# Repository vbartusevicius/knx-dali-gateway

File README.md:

# KNX–DALI Gateway

Open-source DIN-rail gateway between a wired **KNX TP** line and one **DALI / DALI-2** line: up to 64 control gear plus DALI-2 multi-master input devices, commissioned entirely through **ETS**. An optional integrated, isolated DALI bus supply runs from 20–32 V auxiliary DC (a 24 V PSU or the KNX white/yellow pair); the same input also powers the gateway core, with the KNX bus as a seamless fallback. The WiFi dashboard and MQTT are extras: lighting control and ETS provisioning never depend on them.

> [!NOTE]
> **Pre-hardware prototype.** Verified by native unit tests, a Docker KNX/DALI integration lab, KiCad DRC and isolation checks, JLCPCB footprint and pinout checks, and exact-solid CadQuery fit tests. No board has been powered on yet, and no KNX or DALI certification is claimed.

<p align="center">
  <a href="#downloads">Downloads</a> ·
  <a href="#screenshots">Screenshots</a> ·
  <a href="#hardware">Hardware</a> ·
  <a href="#building-one">Building one</a> ·
  <a href="#how-it-works">How it works</a> ·
  <a href="#development">Development</a>
</p>

---

## Downloads

| What | Where | Use |
| --- | --- | --- |
| **First install (USB)** | [`firmware-full-usb.bin`](https://github.com/vbartusevicius/knx-dali-gateway/releases/latest) | Bootloader, partition table and firmware in one image for an empty ESP32-C6. Connect the XIAO over USB-C and write it at `0x0`: `esptool.py --chip esp32c6 write_flash 0x0 firmware-full-usb.bin`. Clears all settings. |
| **Update** | [`firmware.bin`](https://github.com/vbartusevicius/knx-dali-gateway/releases/latest) | Drop it onto the **Firmware** tab of the web interface. Updates firmware and web UI together; settings are kept. |
| **ETS product database** | [`KnxDaliGateway.knxprod`](https://github.com/vbartusevicius/knx-dali-gateway/releases/latest) | Import into ETS 5.7 / 6: 64 lamp channels (DT6/DT7/DT8), 16 groups, broadcast, 8 DALI-2 input devices with up to 4 instances each (1,321 group objects). |
| **Hardware bundles** | [`knx-dali-gateway-v2-hardware.zip` / `v3-hardware.zip`](https://github.com/vbartusevicius/knx-dali-gateway/releases/latest) | Per-variant manufacturing & assembly package (`boards/` with Gerbers, ODB++, BOM/CPL, STEP, KiCad files and renders; `enclosure/` with STLs, STEPs, fit drawings and renders; `assembly_parts.csv` and order CSVs). |
| **Checksums** | [`SHA256SUMS.txt`](https://github.com/vbartusevicius/knx-dali-gateway/releases/latest) | SHA-256 checksums covering every release file above. |

---

## Screenshots

The web interface is built into the firmware and served by the ESP32-C6 itself (live WebSocket updates, no cloud):

<details>
<summary><b>More of the web interface</b>: lamp settings, groups and scenes, error log, bus monitor, settings</summary>

<br>

| Lamp settings | Groups & scenes |
| :---: | :---: |
|  |  |
| Device type, dimming curve, limits, fade, D4i or calculated power, ballast replacement | 16 scenes, 16 groups (G00–G15), group colour, membership written to the ballast |
| **Error log** | **Live DALI bus monitor** |
|  |  |
| Persistent NVS history with remedies | 8/16/24-bit frames and collisions: 1,024 rows on the device, 10,000 in the browser |
| **Settings** | |
|  | |
| WiFi, MQTT with Home Assistant auto-discovery, power model | |

- **Overview:** live level, DT8 colour (Tc, RGBW, xy), per-lamp power (native D4i Part 252 or calculated), lamp finder, fault codes; a second grid for DALI-2 buttons and sensors (IEC 62386-103 / 301–304).
- **Home Assistant:** one gateway device (total power and energy) plus every populated lamp with on/off, dimming, colour, power and fault entities.

</details>

<details>
<summary><b>Front-panel OLED pages</b>: V3 portrait 64×128, V2 landscape 128×64</summary>

<br>

The left button (SCROLL, plain bump) steps through the pages; holding it for 5 s starts the WiFi setup portal. The right button (RESET, bump with an X) reboots on a tap and toggles KNX programming mode when held for 5 s; both held for 10 s is a factory reset.

</details>

---

## Hardware

Two variants share the circuit blocks (`hardware/circuits/blocks/`), the XIAO ESP32-C6 pinout (`gateway/src/firmware/Board.hpp`) and the firmware:

| | **V3** (`v3`) | **V2** (`v2`) |
| --- | --- | --- |
| Width | 1 DIN (18 mm) | 2 DIN (36 mm) |
| Boards | 2: two-sided vertical `main`, front `ui` | 3: `main`, `interface`, `ui` |
| AUX core converter | TRACO TMR 2411 (2 W), on a tongue of `main` in the front protrusion | TRACO TRN 3-2411 (3 W), on the back of `main` |
| DALI terminal | WAGO 2086 push-in (SMD, hand-soldered), buttons beside the wire entries | MX126 screw |
| KNX / AUX | PST 1,0 pin strips (red/black, yellow/white plugs) | PST 1,0 KNX, MX126 screw AUX |
| Display | 0.96" 64×128 portrait SSD1312, solder flex tail | 0.96" 128×64 SSD1306 module, 4-pin header |
| Buttons | Omron B3U pressed through C-shaped spring tabs in the cover | same |
| Main ↔ UI link | 8-pin 0.5 mm FFC (Type B, 50 mm) | 10-pin JST-SH cable |
| Case | Side-opening clamshell, snap-fit | Two 2.5×10 screws, UI snaps |
| Release | [`hardware/releases/v3/`](hardware/releases/v3/README.md) | [`hardware/releases/v2/`](hardware/releases/v2/README.md) |

<details>
<summary><b>V3 renders</b>: assembly and boards</summary>

<br>

PCB artwork: [`main` top](hardware/releases/v3/main/renders/top.svg) · [bottom](hardware/releases/v3/main/renders/bottom.svg) · [`ui` top](hardware/releases/v3/ui/renders/top.svg) · [bottom](hardware/releases/v3/ui/renders/bottom.svg).
Fit drawings: [front](hardware/releases/v3/enclosure/fit_front.svg) · [side](hardware/releases/v3/enclosure/fit_side.svg).

</details>

<details>
<summary><b>V2 renders</b>: assembly and boards</summary>

<br>

PCB artwork: [`main` top](hardware/releases/v2/main/renders/top.svg) · [bottom](hardware/releases/v2/main/renders/bottom.svg) · [`interface` top](hardware/releases/v2/interface/renders/top.svg) · [bottom](hardware/releases/v2/interface/renders/bottom.svg) · [`ui` top](hardware/releases/v2/ui/renders/top.svg) · [bottom](hardware/releases/v2/ui/renders/bottom.svg).
Fit drawings: [front](hardware/releases/v2/enclosure/fit_front.svg) · [side](hardware/releases/v2/enclosure/fit_side.svg).

</details>

Pin table, LED chain and button ladder: [`hardware/docs/variants.md`](hardware/docs/variants.md). Pre-manufacturing reviews: [`review-2026-10-23.md`](hardware/docs/review-2026-10-23.md), [`review-2026-10-22.md`](hardware/docs/review-2026-10-22.md); rework for boards made from `59eea1f`: [`rework-rev-c.md`](hardware/docs/rework-rev-c.md).

---

## Building one

Each `hardware/releases/<variant>/` folder is a complete manufacturing package.

1. **PCBs with SMT assembly (JLCPCB).** Upload `panel/panel_gerbers.zip` (V3: 66.0 × 78.1 mm, 4 layers, 1.2 mm; V2: 98.5 × 76.6 mm, 4 layers, 1.6 mm) with **assembly on both sides**, `panel/panel_bom_jlc.csv` and `panel/panel_cpl_jlc.csv`. You order one PCB and one PCBA job and snap the boards apart. Per-board files are in `main/`, `ui/` (and `interface/` on V2). Compare `renders/top.svg` / `bottom.svg` with JLCPCB's placement preview.
   **Building it yourself:** `order_lcsc.csv` (LCSC BOM tool: map *LCSC Part Number* and *Quantity*) and `order_elsewhere.csv` (electronics LCSC does not sell, with Mouser / Digi-Key / TME numbers) cover every electronic part of one gateway; screws, foam and printed parts are only in `assembly_parts.csv`.
   **Other board houses** (Aisler, PCBWay, Eurocircuits, ...): every folder also has `<board>_odb.zip` (ODB++), Gerbers with drills and an IPC-D-356 netlist in `<board>_gerbers.zip`, and a generic `<board>_bom.csv` / `<board>_cpl.csv` with manufacturer part numbers and KiCad rotations.
2. **Hand-fitted parts.** `assembly_parts.csv` lists everything JLCPCB does not place (Kind `electronics`, `utility` or `printed`), with Mouser, Digi-Key and TME numbers:
   - the XIAO ESP32-C6 (pre-soldered) and its sockets;
   - the RECOM REC3-2415SRW/H2/A/CTRL DALI supply converter;
   - the TRACO AUX core converter;
   - Phoenix PST pin strips and plugs;
   - the OLED, the main-to-UI cable, and two jumper caps for `JP1`.
3. **Case.** Print `enclosure/base.stl` and one cover in PETG or ASA at 0.2 mm layers: `cover.stl`; V2 also has `cover_embossed.stl` (0.6 mm recessed legend). V3 has no front text: the button bumps tell the buttons apart.

<details>
<summary><b>V3 assembly order</b></summary>

1. Lay the OLED face down in the cover recess, fold its flex tail through the UI board's top notch and solder it to `J2`, put the 4 mm foam pad on the UI board, snap the UI board in.
2. Slide `main` into the base from the open left side, so the KNX/AUX pins pass into the right-side pockets and `J3` seats in the top opening.
3. Plug the FFC into `main J4` and `ui J1`, then close the cover over the left side and front until the four side snaps lock.

</details>

---

## How it works

- **KNX side:** an onsemi NCN5130 transceiver (TP1, 9-bit UART) charges a 470 µF store. An SCT2400 buck makes 5 V from it, with an undervoltage lockout above the NCN5130 reset level.
- **Core supply:** the AUX input feeds an isolated TRACO converter (SELV-AUX to SELV-KNX). A leaded priority path prefers it (TLV803 supervisor, 2N7002 and AO3401A switch) and a B5819W Schottky falls back to the KNX buck without a gap. A TI LM66100 keeps USB service power out of the core rail.
- **DALI supply:** the AUX input (PTC, TVS, reverse diode) feeds a RECOM REC3-2415SRW/H2/A/CTRL (24 V → 15 V, functional isolation), then a linear current limiter. The firmware can switch it off through an optocoupler on its `CTRL` pin, and jumper `JP1` disconnects it for an external DALI PSU.
- **DALI transceiver:** TX uses a MOSFET sink with bootstrap gate drive and a 275–350 mA fault clamp. RX uses a zener threshold with a constant-current detector. Both cross a 5.5 mm (reinforced, IEC 60664-1 230 V OVC III) milled barrier through TLP383 optocouplers.
- **Front panel:** the OLED (I2C), two buttons on one ADC ladder, and three WS2812B-MINI-V3J RGB LEDs with gull-wing legs (status, KNX, DALI) behind a 5 V level shifter. All passives are 0805 or larger except three 0603 bus caps next to the NCN5130 on V3; the NCN5130 (QFN-40) is the only leadless chip, as no leaded KNX transceiver exists.

---

## Development

| Folder | Contents |
| --- | --- |
| `gateway/` | ESP32-C6 firmware (C++17, ESP-IDF / PlatformIO) and native unit tests |
| `knxprod/` | ETS product database source and `.knxprod` builder |
| `simulation/` | DALI bus simulator and Docker KNX/DALI integration lab |
| `hardware/` | SKiDL circuits, KiCad layouts, part data, build scripts, release packages |
| `mechanical/` | CadQuery enclosures, fit drawings, front legends, 3D renders |

| Task | Command |
| --- | --- |
| Build, route (fastroute), render, release and test both hardware variants | `python3 hardware/scripts/build.py` |
| One variant or step | `python3 hardware/scripts/build.py v3 --eda` (`--cad`, `--release`, `--test`) |
| Refresh the README images (after a release) | `docker compose --profile hardware run --rm -T cad "python3 mechanical/scripts/readme_images.py"` |
| Firmware tests and ESP32-C6 build (writes `firmware.bin` and `firmware-full-usb.bin`) | `pio test -d gateway -e native && pio run -d gateway -e dev_c6 -e release_c6` |
| Refresh the clangd compilation database | `pio run -d gateway -e dev_c6 -t compiledb` |
| Integration lab | `simulation/run-tests.sh` |
| ETS package | `ETS_CV_DIR=knxprod/ETS knxprod/scripts/package.sh` |
| Stage GitHub release assets + `SHA256SUMS.txt` | `python3 scripts/package_release.py --clean` |
| Lint Python (ruff) | `docker compose --profile lint run --rm lint check .` |
| Lint C++ (clang-format, clang-tidy) | `docker compose --profile lint run --rm cpp-lint gateway/scripts/check_cpp.sh` |

Licences per folder: [`LICENSE.md`](LICENSE.md). Contributor and coding-agent instructions (rules, commands, requirements): [`AGENTS.md`](AGENTS.md). Design background and research history: [`docs/research-notes.md`](docs/research-notes.md).

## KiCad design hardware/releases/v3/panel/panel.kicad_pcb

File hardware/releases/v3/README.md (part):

# KNX-DALI gateway hardware v3 (1 DIN, two boards)

**Revision D (2026-10-22).** Changes against rev C (`59eea1f`, the first order): AUX-powered core (TRACO TMR 1-2411 U9 isolated converter, hand-fitted, plus TI TPS2121 U10 priority mux with the KNX buck as fallback); XIAO LM66100 U7 CE on VOUT (no USB back-feed); DALI TX clamp 2R, gate divider 4k7/10k, RX pull-up 4k7, buck EN 100k; enclosure with channels over the back-side diodes, board edge reliefs, backing ribs, C-shaped spring button tabs with front bumps and plungers, OLED supports beside the panel, longer DALI terminal slot; through-hole leads trimmed to 1.5 mm; a base right-wall recess over U9. Rev C boards and prints: follow [`hardware/docs/rework-rev-c.md`](../../docs/rework-rev-c.md) (pins in `rework/`). NCN5130 cluster re-placed to the datasheet layout rules (C1/C2/C3/C5/C15, L1).

**Hand-assembly revision (2026-11-11).** Every part is chosen for soldering with an iron:
- **Passives:** all 0805 or larger. The one exception is v3's three NCN5130 bus caps (C1 47 nF, C2 100 nF, C3 220 nF), which are 0603 so the chip's left side stays routable.
- **LEDs:** WS2812B-MINI-V3J with gull-wing legs (LCSC C22371519).
- **Crystal:** 2-pad 5032.
- **Core power path:** leaded parts (TLV803M U10, 2N7002 Q10, AO3401A Q9, B5819W D11) replace the VQFN TPS2121.
- **Still fine-pitch:** the NCN5130 (QFN-40; no leaded KNX transceiver exists: hot plate or hot air) and the LM66100 (SC-70-6, leaded).
- **Isolation:** DALI isolation is 5.5 mm (reinforced, IEC 60664-1 230 V OVC III PD2); SELV-AUX to SELV-KNX is 1 mm (functional).
- **Buttons:** left = SCROLL (plain bump), right = RESET (X bump).
- **USB service:** the XIAO is turned so its USB-C faces the main board's rail-side edge (x 38.1, 1.7 mm from the edge, nothing tall in the path). Lift main out of the base to plug in: with the board in the base the plug overmould does not fit under the right wall. test_usb_access.py keeps the plug path clear.
- `<board>/<board>_assembly.pdf`: hand-soldering guide. One page per populated side (the bottom mirrored, as seen from below), each part's body, reference and value, a red dot on pin 1, a black corner on hand-fitted parts and one colour per value. Large parts are dashed under the small ones. A values page lists quantity, side and references.

Generated by `HARDWARE_VARIANT=v3 python3 hardware/scripts/release.py v3` from
`hardware/layout/v3/`, with the same gates as v2: KiCad DRC 0 errors and 0
unrouted, every part orderable or hand-fit, every JLC part checked against
JLCPCB's part record, live stock and its EasyEDA footprint (pin for pin; the
placement file carries the fitted rotations and centres). CI
(`HARDWARE_VARIANT=v3`, `test_release_current.py`) fails as soon as either board
no longer matches this release.

| Board | Size | Layers | Thickness | Position in the case | Folder |
|---|---|---|---|---|---|
| **Breakaway Panel (`panel`)** | **55.6 x 78.0 mm** | **4** | **1.2 mm** | **Combined `main` + `ui` on one PCB with mouse-bite breakaway tabs (1 PCB + 1 PCBA order)** | **`panel/`** |
| Main (`main`) | 39.8 x 78.0 mm | 4 | 1.2 mm | vertical along the left side wall (two-sided): tall parts on the front (+x: KNX/AUX/DALI push-in pin strips, 470 uF SMD cap, 220 uH inductor, XIAO on 5 mm sockets with 5 V buck underneath, REC3-2415SRW/H2/A/CTRL, JP1, DALI bridge/pass transistor/optocouplers, UI FFC), low SMD parts on the back (-x, inside the THT solder-tail shadow: NCN5130 + crystal + passives, DALI TX/RX passives & transistors) | `main/` |
| UI (`ui`) | 13.8 x 40.5 mm | 4 | 1.2 mm | snapped into the cover protrusion: 0.96" 64x128 portrait SSD1312 OLED (QG-6428TSWCG02 / JLX12864OLED-S096W / NFP1312-15AY, 14.0 x 28.0 mm) soldered to the 14-pad 0.62 mm pitch footprint on the back with 3.3 V charge-pump passives, two Omron B3U-1000P buttons with 1.4 mm protruding caps, three RGB LEDs in a row below the buttons, 8-pin FFC to main | `ui/` |

A single 8-pin 0.5 mm **Type B (reverse / opposite-side contacts)** FFC cable (`SHOU HAN FFC-0.5-8P-50mm-B`, LCSC `C42416274`, 50 mm) connects `main` J4 to `ui` J1 (since both `J4` and `J1` are bottom-contact FFC connectors with Pin 1 on the same side, a Type B reverse cable connects Pin 1 `+3V3` to Pin 1 `+3V3`).

## Ordering at JLCPCB

1. **Recommended — Order as 1 Breakaway Panel (`panel/`):**
   - Upload `panel/panel_gerbers.zip` and select **4 layers, `1.2 mm` PCB Thickness** on JLCPCB's order page (note: JLCPCB's web form always defaults the thickness radio button to `1.6 mm` until you click **`1.2`**).
   - Enable **PCB Assembly (Both Sides)** and upload `panel/panel_bom_jlc.csv` + `panel/panel_cpl_jlc.csv`.
2. **Or Order as Separate Boards (`main/` and `ui/`):**
   - Upload `main/main_gerbers.zip` and `ui/ui_gerbers.zip` (4 layers, **1.2 mm**).
   - Upload `<board>_bom_jlc.csv` + `<board>_cpl_jlc.csv`.
3. `<board>_assembly_check.csv` (and `panel/panel_assembly_check.csv`) lists JLCPCB footprint, rotation and stock for
   every part.

## Ordering elsewhere (Aisler, PCBWay, Eurocircuits, ...)

Each board folder and `panel/` also holds fab-independent files:

- `<board>_odb.zip`: ODB++ (copper, drills, outline, netlist, component
  placement). Aisler's preferred upload; PCBWay and Eurocircuits accept it.
- `<board>_gerbers.zip`: Gerber X2 per layer, Excellon drills (plated and
  non-plated) and `<board>.d356`, the IPC-D-356 netlist for the electrical test.
- `<board>_bom.csv`: every part with value, footprint, manufacturer part number
  (LCSC number for reference), SMD/THT, and whether the assembler or you fit it.
- `<board>_cpl.csv`: placement of the assembled parts in KiCad's coordinates
  and rotations (the `_jlc` files use JLCPCB's rotations and are for JLCPCB only).

Order the stack-up, thickness and finish given above; check the assembler's
placement preview for the bottom-side and rotated parts as for JLCPCB.

## Ordering the parts yourself

For one complete gateway (all boards and hand-fit parts), in this folder:

- `order_lcsc.csv`: LCSC BOM tool (lcsc.com → BOM Tool, map **LCSC Part Number** and
  **Quantity**). Every board part plus the hand-fit parts LCSC sells; one line per LCSC number,
  designators as `board:ref`. Multiply the quantities for more gateways; LCSC rounds up to each
  part's minimum order.
- `order_elsewhere.csv`: the electronics LCSC does not sell (XIAO, REC3, converters, Phoenix pin
  strips and plugs, OLED, cable), with every Mouser / Digi-Key / TME number. A cell may list
  alternatives, e.g. `713-102010636 (or 713-113991254)`; buy one of them.
- `assembly_parts.csv`: everything not placed by the assembler, with a **Kind** column:
  `electronics` (the hand-fit parts above), `utility` (screws, foam pad, lead trimming) and
  `printed` (case parts). Utility and printed items are not in the order files; get them locally.

Not needed when JLCPCB assembles the boards: then order only the hand-fit lines.

## Hand-fitted parts (`<board>_hand_fit.csv`)

- `main` J1, J2: two **Phoenix Contact 1574200** (PST 1,0/2-5,75) pin strips on
  the bottom shoulder of `main` (pins pointing +x to the right). The red/black KNX
  plug (front) and the yellow/grey 20-32 V AUX plug (rear) go in from the right
  side into pockets sized for the WAGO 243-211 (11.5 x 10.2 x 10.2 mm, measured,
  0.3 mm clearance all round, a slot for the butterfly key on the lower wall)
  and sit on the strips, where their sockets meet the pins. Their wire entries
  face down, about 2.8 mm inside the open bottom of the pockets. With the
  11.5 mm plug, about 1 mm of it stands out of the case's right side: leave
  that gap to the next device on the rail.
- `main` J3: **WAGO 2086-1202/700-000/997-604**, the 2-pole 3.5 mm SMD DALI
  push-in terminal. Hand-solder it (JLCPCB has none in stock; Digi-Key
  `2946-2086-1202/700-000/997-604CT-ND`). Its wire entries and both release
  buttons are in the face that sits in the top-wall opening: press a button
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
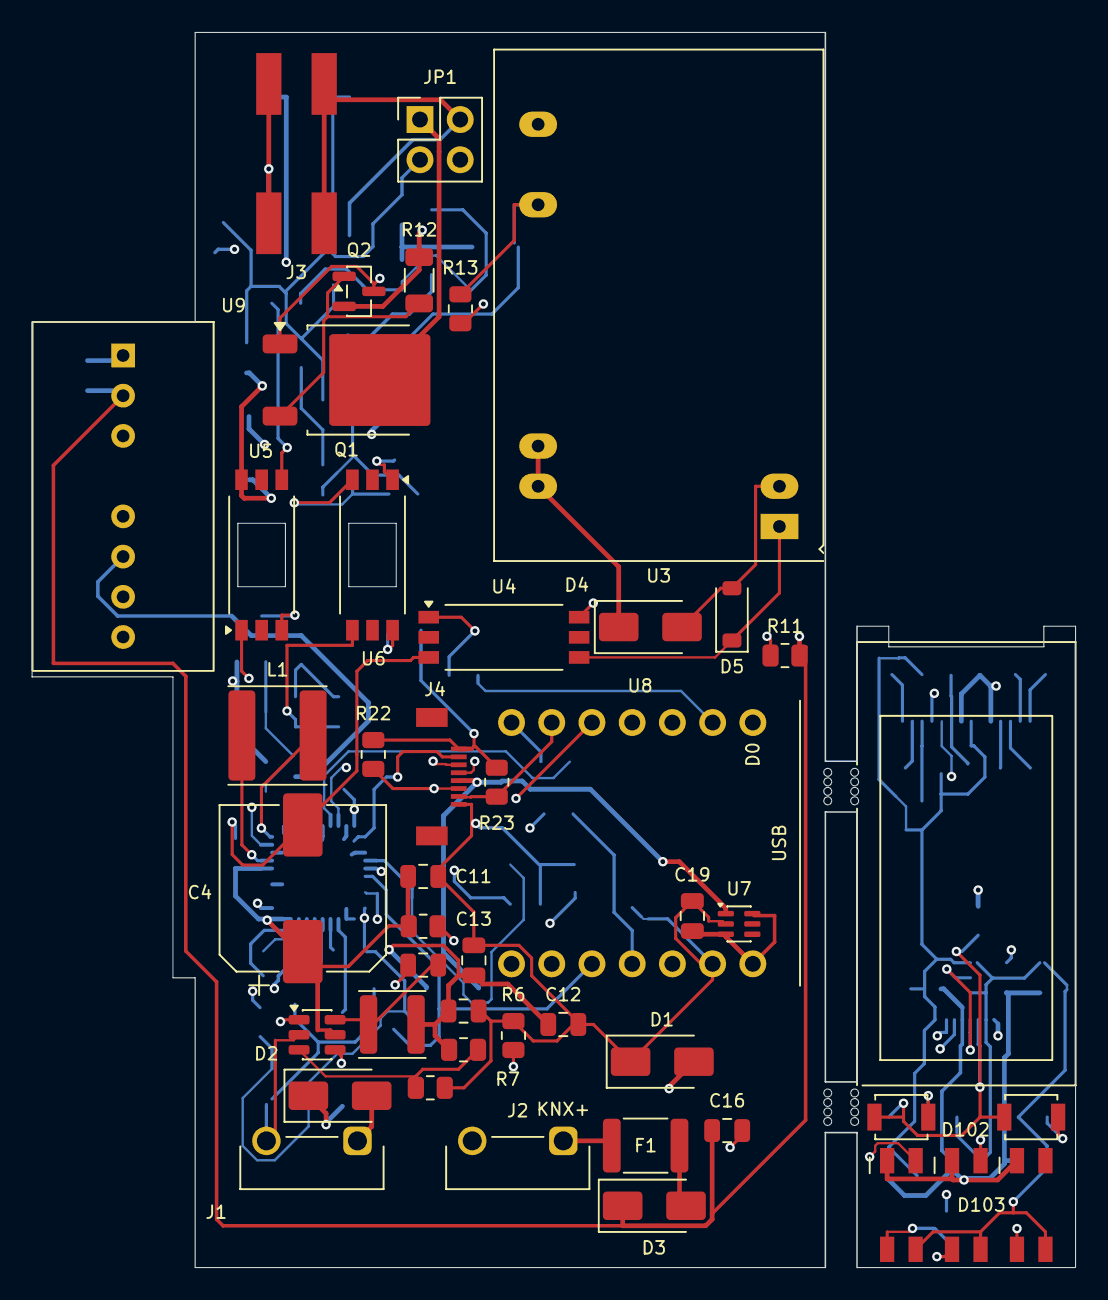
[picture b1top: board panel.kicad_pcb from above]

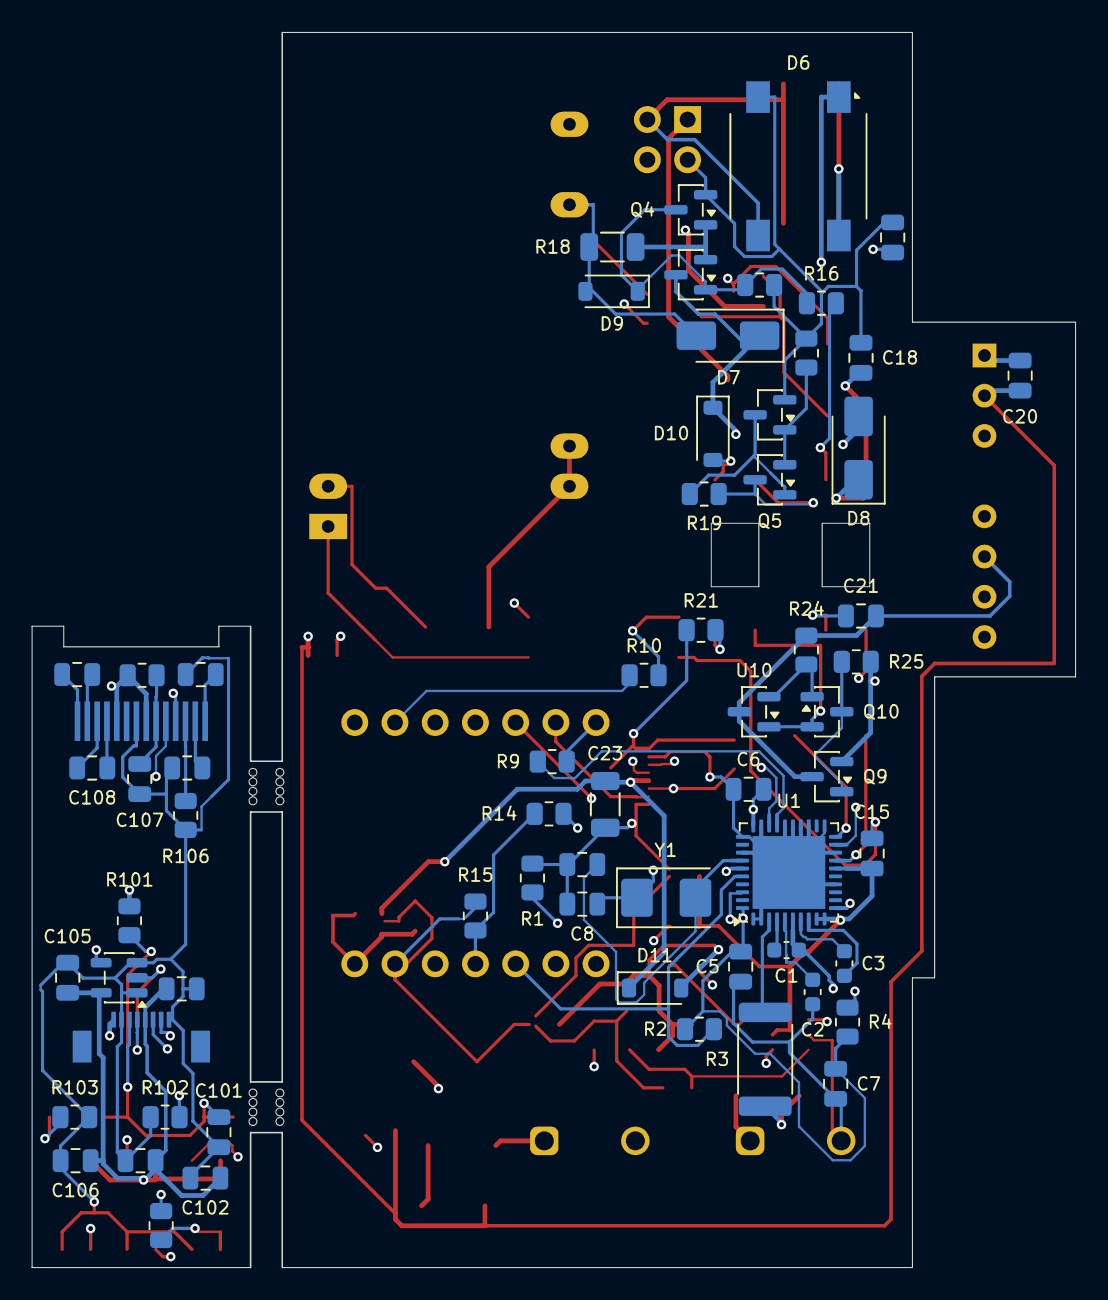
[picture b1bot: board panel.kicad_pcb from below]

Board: 4 copper layers, 65.9 x 78.0 mm, 126 parts (65 on the bottom side), 82 nets.

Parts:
C1: 47n 50V; C_0603_1608Metric
C2: 100n 50V; C_0603_1608Metric
C3: 220n 50V; C_0603_1608Metric
C4: 470u 35V; CP_Elec_10x10
C5, C6, C10, C14, C101, C103, C104, C105, C106, C107: 100n 50V; C_0805_2012Metric
C7, C12, C13: 22u 25V; C_0805_2012Metric
C8, C9: 33p C0G 50V; C_0805_2012Metric
C11, C16, C20: 10u 50V; C_0805_2012Metric
C15, C18, C102, C108, C109, C110, C111: 1u 50V; C_0805_2012Metric
C17, C19, C21: 10u 25V; C_0805_2012Metric
C23: 100u 6.3V; C_1206_3216Metric
D1: SMAJ40CA; D_SMA
D2, D3, D8: SS16; D_SMA
D4: SMAJ33A; D_SMA
D5, D10: 5V6; D_SOD-123
D6: DF06S; Diode_Bridge_Vishay_DFS
D7: SMAJ24A; D_SMA
D9: 12V; D_SOD-123
D11: B5819W; D_SOD-123
D101: RGB STATUS; LED_WS2812B-MINI-V3J_3.5x3.5mm
D102: RGB KNX; LED_WS2812B-MINI-V3J_3.5x3.5mm
D103: RGB DALI; LED_WS2812B-MINI-V3J_3.5x3.5mm
F1: 1.1A; Fuse_1812_4532Metric
J1: KNX bus terminal pins; Phoenix_PST_1,0-2-5,75_R32_1x02_P5.75mm
J2: AUX 20-32 V (yellow/white); Phoenix_PST_1,0-2-5,75_R32_1x02_P5.75mm
J3: DALI bus (push-in); TerminalBlock_WAGO_2086-1202_SMD
J4: UI board; FPC_Kinghelm_KH-FPC0.5-H1.2SMT-8P
J101: Carrier; FPC_Kinghelm_KH-FPC0.5-H1.2SMT-8P
J102: OLED; OLED_FPC_14P_P0.62mm_Hotbar
JP1: DALI supply; PinHeader_2x02_P2.54mm_Vertical
L1: 220uH; L_Sunlord_SWPA6045S
L2: 4.7uH; L_APV_ANR4012
MB1, MB2, MB3, MB4, MB5, MB6, MB7, MB8, MB9, MB10, MB11, MB12, MB13, MB14, MB15, MB16: DNP
Q1: MJD45H11; TO-252-2
Q2: BC857; SOT-23
Q3: IRLML0060; SOT-23
Q4, Q5, Q6: BC847; SOT-23
Q9: AO3401A; SOT-23
Q10: 2N7002; SOT-23
R1, R6, R8: 10k 1%; R_0805_2012Metric
R2, R11, R15, R17, R25, R101, R102, R105: 10k; R_0805_2012Metric
R3: 27R; R_2512_6332Metric
R4: 1R; R_0805_2012Metric
R5: 100k 1%; R_0805_2012Metric
R7: 51k 1%; R_0805_2012Metric
R9: 1k; R_0805_2012Metric
R10, R14, R104: 330R; R_0805_2012Metric
R12: 3R3; R_1206_3216Metric
R13, R16, R21, R22, R23: 4k7; R_0805_2012Metric
R18: 2R; R_1206_3216Metric
R19, R24: 100k; R_0805_2012Metric
R20: 680R; R_0805_2012Metric
R103: 20k; R_0805_2012Metric
R106: 390k; R_0805_2012Metric
SW101: SCROLL; SW_SPST_B3U-1000P
SW102: RESET; SW_SPST_B3U-1000P
U1: NCN5130MNTWG; QFN-40-1EP_6x6mm_P0.5mm_EP4.6x4.6mm
U2: SCT2400TVBR; TSOT-23-6
U3: REC3-2415SRW/H2/A/CTRL 24V->15V 3W iso; Converter_DCDC_RECOM_REM3_DIP24_CTRL
U4: TLP383; SO-6L_10x3.84mm_P1.27mm
U5, U6: TLP383(D4BLLTL,E; SO-6L_10x3.84mm_P1.27mm
U7: LM66100; SOT-363_SC-70-6
U8: XIAO ESP32C6; XIAO_ESP32C6_Header
U9: TMR 2411 24V->5V 2W iso; Converter_DCDC_TRACO_TMR2_SIP8
U10: TLV803M supervisor; SOT-23
U101: 74AHCT1G125; SOT-23-5
Y1: 16MHz; Crystal_SMD_5032-2Pin_5.0x3.2mm

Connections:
+3V3: J4.1, R21.1, R22.1, R23.1, U8.12
+3V3_TRX: C5.1, C6.1, C7.1, R2.1, R4.2, U1.11, U1.19, U1.30, U1.40
+5V: C23.1, D11.1, J4.5, Q9.2, R25.1, U7.1
+5V_AUX: C21.1, Q9.3, R24.1, U9.6, U10.3
+5V_BUCK: C12.1, C13.1, C14.1, D11.2, L2.2, R7.1
+5V_XIAO: C19.1, U7.3, U7.6, U8.14
AUX_FUSED: D3.2, F1.2
AUX_IN: F1.1, J2.1
AUX_P: C16.1, C20.1, D3.1, D4.1, R11.1, U3.22, U3.23, U9.2
BTN_LADDER: J4.3, U8.3
CAV: C2.1, U1.5
CCP: C1.2, U1.4
CEQ1: C3.1, U1.7
CEQ2: C3.2, U1.8
CORE_AUX_GOOD: Q10.1, R24.2, U10.2
CORE_PFET_G: Q9.1, Q10.3, R25.2
DA1: D6.3, J3.1, JP1.2
DA2: D6.4, J3.2, JP1.4
DALI_BOOT: C18.1, D8.1, U5.6
DALI_GATE: D9.1, Q3.1, Q4.3, R16.2, R17.1
DALI_GATE_SW: R16.1, U5.4
DALI_ISO15V: C17.1, Q2.2, R12.1, U3.14
DALI_RX: R21.2, U6.6, U8.9
DALI_SENSE: Q3.2, Q4.1, R18.1
DALI_SUPPLY_OFF: R10.1, U8.2
DALI_SUPPLY_SW: JP1.1, Q1.2
DALI_TX: R14.1, R15.1, U8.11
DA_P: D6.1, D7.1, D8.2, D10.1, Q3.3
FANIN: R1.1, U1.38
GND: C2.2, C4.2, C5.2, C6.2, C7.2, C8.2, C9.2, C11.2, C12.2, C13.2, C14.2, C15.2, C19.2, C21.2, C23.2, D1.1, J1.2, J4.2, J4.8, Q10.2, R1.2, R6.2, R8.2, R15.2, U1.1, U1.2, U1.14, U1.18, U1.21, U1.23, U1.24, U1.25, U1.26, U1.29, U1.31, U1.33, U1.41, U2.2, U4.3, U5.3, U6.4, U7.2, U8.13, U9.7, U10.1
GNDA: C16.2, C20.2, D4.2, D5.2, J2.2, U3.2, U9.1
GNDD: C17.2, C18.2, D6.2, D7.2, D9.2, JP1.3, Q4.2, Q6.2, R13.2, R17.2, R18.2, R20.2, U3.16
I2C_SCL: J4.7, R23.2, U8.6
I2C_SDA: J4.6, R22.2, U8.5
KNX_P: D1.2, D2.2, J1.1
KNX_P_PROT: C1.1, D2.1, R3.1, U1.6
KNX_RXD: R9.1, U8.7
KNX_TXD: U1.28, U8.8
LED_DATA: J4.4, U8.1
unnamed: R5.2, R6.1, U2.4
unnamed: C10.1, U2.1
unnamed: R7.2, R8.1, U2.3
unnamed: R9.2, U1.27
unnamed: R10.2, U4.1
unnamed: R11.2, U4.6
unnamed: D5.1, U3.1, U4.4
unnamed: Q1.3, Q2.1, R12.2
unnamed: Q1.1, Q2.3, R13.1
unnamed: R14.2, U5.1
unnamed: D10.2, U6.1
unnamed: Q5.2, Q6.1, R20.1
unnamed: Q5.1, Q6.3, R19.2
NCN_SAVEB: R2.2, U1.36, U8.10
RX_LIM_IN: Q5.3, R19.1, U6.3
SW: C10.2, L2.1, U2.6
TX0: R3.2, U1.3
UI_+3V3: J101.1, J102.5, J102.8, R101.1, R105.1
UI_+5V: C102.1, C103.1, C104.1, C105.1, C106.1, D101.1, D102.1, D103.1, J101.5, U101.5
UI_BTN_LADDER: C101.1, J101.3, R101.2, SW101.1, SW102.1
UI_GND: C101.2, C102.2, C103.2, C104.2, C105.2, C106.2, C107.2, C110.2, C111.2, D101.3, D102.3, D103.3, J101.2, J101.8, J102.7, R102.2, R103.2, R106.2, U101.1, U101.3
UI_I2C_SCL: J101.7, J102.10
UI_I2C_SDA: J101.6, J102.11
UI_LED_CHAIN1: D101.2, D102.4
UI_LED_CHAIN2: D102.2, D103.4
UI_LED_DATA: J101.4, U101.2
UI_N$1: R102.1, SW101.2
UI_N$2: R103.1, SW102.2
UI_N$3: R104.1, U101.4
UI_N$4: D101.4, R104.2
UI_OLED_C1N: C108.2, J102.4
UI_OLED_C1P: C108.1, J102.3
UI_OLED_C2N: C109.2, J102.2
UI_OLED_C2P: C109.1, J102.1
UI_OLED_IREF: J102.12, R106.1
UI_OLED_RES: C107.1, J102.9, R105.2
UI_OLED_VCOMH: C110.1, J102.13
UI_OLED_VOUT: C111.1, J102.14
VDD1M: L1.2, R4.1, U1.20
VFILT: C4.1, C11.1, C15.1, R5.1, U1.9, U1.10, U1.16, U2.5
VSW1: L1.1, U1.17
XTAL1: C8.1, U1.35, Y1.1
XTAL2: C9.1, U1.34, Y1.2

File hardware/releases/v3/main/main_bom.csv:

Designator,Quantity,Value,Footprint,Manufacturer Part Number,LCSC Part #,Mount,Fitted by
F1,1,1.1A,Fuse_1812_4532Metric,1812L110/33MR,C142747,SMD,assembler
"R19,R24",2,100k,R_0805_2012Metric,0805W8F1003T5E,C149504,SMD,assembler
R5,1,100k 1%,R_0805_2012Metric,0805W8F1003T5E,C149504,SMD,assembler
C2,1,100n 50V,C_0603_1608Metric,CC0603KRX7R9BB104,C14663,SMD,assembler
"C10,C14,C5,C6",4,100n 50V,C_0805_2012Metric,CC0805KRX7R9BB104,C49678,SMD,assembler
C23,1,100u 6.3V,C_1206_3216Metric,CL31A107MQHNNNE,C15008,SMD,assembler
"R11,R15,R17,R2,R25",5,10k,R_0805_2012Metric,0805W8F1002T5E,C17414,SMD,assembler
"R1,R6,R8",3,10k 1%,R_0805_2012Metric,0805W8F1002T5E,C17414,SMD,assembler
"C17,C19,C21",3,10u 25V,C_0805_2012Metric,CL21A106KAYNNNE,C15850,SMD,assembler
"C11,C16,C20",3,10u 50V,C_0805_2012Metric,GRM21BR61H106KE43L,C440198,SMD,assembler
D9,1,12V,D_SOD-123,MMSZ12T1G,C72599,SMD,assembler
Y1,1,16MHz,Crystal_SMD_5032-2Pin_5.0x3.2mm,TAXM16M2QLFCDT1T,C122519,SMD,assembler
R4,1,1R,R_0805_2012Metric,0805W8F100KT5E,C25271,SMD,assembler
R9,1,1k,R_0805_2012Metric,0805W8F1001T5E,C17513,SMD,assembler
"C15,C18",2,1u 50V,C_0805_2012Metric,CL21B105KBFNNNE,C28323,SMD,assembler
C3,1,220n 50V,C_0603_1608Metric,CL10B224KB8NNNC,C64705,SMD,assembler
L1,1,220uH,L_Sunlord_SWPA6045S,SWPA6045S221MT,C91047,SMD,assembler
"C12,C13,C7",3,22u 25V,C_0805_2012Metric,CL21A226MAQNNNE,C45783,SMD,assembler
R3,1,27R,R_2512_6332Metric,25121WJ0270T4E,C25478,SMD,assembler
Q10,1,2N7002,SOT-23,2N7002,C8545,SMD,assembler
R18,1,2R,R_1206_3216Metric,1206W4F200KT5E,C17942,SMD,assembler
"R10,R14",2,330R,R_0805_2012Metric,0805W8F3300T5E,C17630,SMD,assembler
"C8,C9",2,33p C0G 50V,C_0805_2012Metric,0805CG330J500NT,C157687,SMD,assembler
R12,1,3R3,R_1206_3216Metric,1206W4F330KT5E,C17945,SMD,assembler
L2,1,4.7uH,L_APV_ANR4012,SMNR4012-4R7MT,C135248,SMD,assembler
C4,1,470u 35V,CP_Elec_10x10,RYRVT35V470UF10*10,C48970703,SMD,assembler
C1,1,47n 50V,C_0603_1608Metric,CL10B473KB8NNNC,C1622,SMD,assembler
"R13,R16,R21,R22,R23",5,4k7,R_0805_2012Metric,0805W8F4701T5E,C17673,SMD,assembler
R7,1,51k 1%,R_0805_2012Metric,0805W8F5102T5E,C17737,SMD,assembler
"D10,D5",2,5V6,D_SOD-123,MMSZ5V6T1G,C236111,SMD,assembler
R20,1,680R,R_0805_2012Metric,0805W8F6800T5E,C17798,SMD,assembler
Q9,1,AO3401A,SOT-23,AO3401A,C15127,SMD,assembler
D11,1,B5819W,D_SOD-123,B5819W SL,C8598,SMD,assembler
"Q4,Q5,Q6",3,BC847,SOT-23,BC847B,C57668,SMD,assembler
Q2,1,BC857,SOT-23,BC857C,C181147,SMD,assembler
JP1,1,DALI supply,PinHeader_2x02_P2.54mm_Vertical,2.54-2*2PPin,C66690,THT,assembler
D6,1,DF06S,Diode_Bridge_Vishay_DFS,DF06S-T,C460867,SMD,assembler
Q3,1,IRLML0060,SOT-23,IRLML0060TRPBF,C67274,SMD,assembler
U7,1,LM66100,SOT-363_SC-70-6,LM66100DCKR,C2869734,SMD,assembler
Q1,1,MJD45H11,TO-252-2,MJD45H11,C48580717,SMD,assembler
U1,1,NCN5130MNTWG,QFN-40-1EP_6x6mm_P0.5mm_EP4.6x4.6mm,NCN5130MNTWG,C513000,SMD,assembler
U2,1,SCT2400TVBR,TSOT-23-6,SCT2400TVBR,C2693819,SMD,assembler
D7,1,SMAJ24A,D_SMA,SMAJ24A,C148222,SMD,assembler
D4,1,SMAJ33A,D_SMA,SMAJ33A,C113966,SMD,assembler
D1,1,SMAJ40CA,D_SMA,SMAJ40CA,C113970,SMD,assembler
"D2,D3,D8",3,SS16,D_SMA,SS16,C2481,SMD,assembler
U4,1,TLP383,SO-6L_10x3.84mm_P1.27mm,"TLP383(D4BLLTL,E",C3002263,SMD,assembler
"U5,U6",2,"TLP383(D4BLLTL,E",SO-6L_10x3.84mm_P1.27mm,"TLP383(D4BLLTL,E",C3002263,SMD,assembler
U10,1,TLV803M supervisor,SOT-23,TLV803MDBZR-TP,C52817175,SMD,assembler
J4,1,UI board,FPC_Kinghelm_KH-FPC0.5-H1.2SMT-8P,KH-FPC0.5-H1.2SMT-8P-QCHF,C48532769,SMD,assembler
J2,1,AUX 20-32 V (yellow/white),"Phoenix_PST_1,0-2-5,75_R32_1x02_P5.75mm",1574200,,THT,hand-fit (not assembled)
J3,1,DALI bus (push-in),TerminalBlock_WAGO_2086-1202_SMD,2086-1202/700-000/997-604,,SMD,hand-fit (not assembled)
J1,1,KNX bus terminal pins,"Phoenix_PST_1,0-2-5,75_R32_1x02_P5.75mm",1574200,,THT,hand-fit (not assembled)
U3,1,REC3-2415SRW/H2/A/CTRL 24V->15V 3W iso,Converter_DCDC_RECOM_REM3_DIP24_CTRL,REC3-2415SRW/H2/A/CTRL,,THT,hand-fit (not assembled)
U9,1,TMR 2411 24V->5V 2W iso,Converter_DCDC_TRACO_TMR2_SIP8,TMR 2411,,THT,hand-fit (not assembled)
U8,1,XIAO ESP32C6,XIAO_ESP32C6_Header,102010636,,THT,hand-fit (not assembled)

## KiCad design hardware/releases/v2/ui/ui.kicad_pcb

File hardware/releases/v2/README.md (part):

# KNX-DALI gateway hardware v2 (2 DIN, three boards)

**Revision C (2026-10-22).** Changes against rev B (`59eea1f`): AUX-powered core (TRACO TMR 1-2411 U9 on the back of main, hand-fitted, plus TI TPS2121 U10 priority mux with the KNX buck as fallback; U4 and C4 moved); XIAO LM66100 U7 (UI) CE on VOUT (no USB back-feed); DALI TX clamp 2R, gate divider 4k7/10k, RX pull-up 4k7 (interface), buck EN 100k (main); cover screw tab centred between the terminals and lips notched at the terminal bodies. Rev B boards and prints: follow [`hardware/docs/rework-rev-c.md`](../../docs/rework-rev-c.md).

**Hand-assembly revision (2026-11-11).** Every part is chosen for soldering with an iron:
- **Passives:** all 0805 or larger. The one exception is v3's three NCN5130 bus caps (C1 47 nF, C2 100 nF, C3 220 nF), which are 0603 so the chip's left side stays routable.
- **LEDs:** WS2812B-MINI-V3J with gull-wing legs (LCSC C22371519).
- **Crystal:** 2-pad 5032.
- **Core power path:** leaded parts (TLV803M U10, 2N7002 Q10, AO3401A Q9, B5819W D11) replace the VQFN TPS2121.
- **Still fine-pitch:** the NCN5130 (QFN-40; no leaded KNX transceiver exists: hot plate or hot air) and the LM66100 (SC-70-6, leaded).
- **Isolation:** DALI isolation is 5.5 mm (reinforced, IEC 60664-1 230 V OVC III PD2); SELV-AUX to SELV-KNX is 1 mm (functional).
- **Buttons:** left = SCROLL (plain bump), right = RESET (X bump).
- `<board>/<board>_assembly.pdf`: hand-soldering guide. One page per populated side (the bottom mirrored, as seen from below), each part's body, reference and value, a red dot on pin 1, a black corner on hand-fitted parts and one colour per value. Large parts are dashed under the small ones. A values page lists quantity, side and references.

Generated by `HARDWARE_VARIANT=v2 python3 hardware/scripts/release.py` from
`hardware/layout/v2/`, with the gates of every release: KiCad DRC 0 errors and 0
unrouted, every part orderable or hand-fit, every JLC part checked against
JLCPCB's part record, live stock and its EasyEDA footprint (pin for pin; the
placement file carries the fitted rotations and centres). CI
(`HARDWARE_VARIANT=v2`, `test_release_current.py`) fails as soon as the boards
no longer match this release.

| Board | Size | Layers | Position in the case | Folder |
|---|---|---|---|---|
| Main | 31.5 x 76.5 mm | 4 | flat in the base: KNX, 5 V, isolated DALI supply, all terminals | `main/` |
| Interface | 31.5 x 27.5 mm | 4 | plugged onto main (11 mm above it): isolated DALI TX/RX | `interface/` |
| UI | 31.5 x 40.5 mm | 4 | snapped into the cover: XIAO ESP32-C6, OLED, 2 buttons, 3 RGB LEDs | `ui/` |

The interface board has no case retention of its own: its two male headers
(J1 logic, J2 DALI, on its back) plug into main J6/J5 (8.5 mm sockets +
2.5 mm header plastic = 11.0 mm). DALI TX/RX reach it from the XIAO through
the main-to-UI cable (pins 7/8) and main J6. The only cable is that 10-pin
JST-SH jumper.

## Ordering at JLCPCB

1. Upload `<board>_gerbers.zip`: 4 layers, 1.6 mm, all three boards
   (standard JLC04161H-7628 stack-up; main has 0.2 mm thermal vias).
2. PCB Assembly, both sides: `<board>_bom_jlc.csv` + `<board>_cpl_jlc.csv`.
   Through-hole parts in the BOMs (main J5/J6 sockets and JP1, interface J1/J2
   headers on its back, terminals J2/J3) go to JLC's THT service.
3. `<board>_assembly_check.csv` lists JLCPCB footprint, rotation and stock for
   every part. Glance at the placement preview for the bottom-side parts
   (main: C3, L1, R1-R3; interface: C1, D1, D2, J1, J2, R4, R5, R7; UI: C5,
   C7, J1); their rotation follows JLCPCB's documented bottom convention.
   Pin 1 / polarity: optocouplers, transistors, the bridge's + corner, WS2812B-MINI-V3J
   corner marks, diode bands.

## Ordering elsewhere (Aisler, PCBWay, Eurocircuits, ...)

Each board folder and `panel/` also holds fab-independent files:

- `<board>_odb.zip`: ODB++ (copper, drills, outline, netlist, component
  placement). Aisler's preferred upload; PCBWay and Eurocircuits accept it.
- `<board>_gerbers.zip`: Gerber X2 per layer, Excellon drills (plated and
  non-plated) and `<board>.d356`, the IPC-D-356 netlist for the electrical test.
- `<board>_bom.csv`: every part with value, footprint, manufacturer part number
  (LCSC number for reference), SMD/THT, and whether the assembler or you fit it.
- `<board>_cpl.csv`: placement of the assembled parts in KiCad's coordinates
  and rotations (the `_jlc` files use JLCPCB's rotations and are for JLCPCB only).

Order the stack-up, thickness and finish given above; check the assembler's
placement preview for the bottom-side and rotated parts as for JLCPCB.

## Ordering the parts yourself

For one complete gateway (all boards and hand-fit parts), in this folder:

- `order_lcsc.csv`: LCSC BOM tool (lcsc.com → BOM Tool, map **LCSC Part Number** and
  **Quantity**). Every board part plus the hand-fit parts LCSC sells; one line per LCSC number,
  designators as `board:ref`. Multiply the quantities for more gateways; LCSC rounds up to each
  part's minimum order.
- `order_elsewhere.csv`: the electronics LCSC does not sell (XIAO, REC3, converters, Phoenix pin
  strips and plugs, OLED, cable), with every Mouser / Digi-Key / TME number. A cell may list
  alternatives, e.g. `713-102010636 (or 713-113991254)`; buy one of them.
- `assembly_parts.csv`: everything not placed by the assembler, with a **Kind** column:
  `electronics` (the hand-fit parts above), `utility` (screws, foam pad, lead trimming) and
  `printed` (case parts). Utility and printed items are not in the order files; get them locally.

Not needed when JLCPCB assembles the boards: then order only the hand-fit lines.

## Front legend (optional print)

Three flat faces carry the legend (3 mm letters, 0.6 mm deep): bottom shoulder (KNX only: the keyed plug fits one way round), front (SCROLL,
RESET; the LEDs are unmarked: STATUS, KNX, DALI from left to right) and top shoulder (- + "20-32V" and DA DA "BUS", enclosed by one bracket
with DALI in its bar: this input feeds only the internal DALI bus supply,
not the gateway). 20-32 V keeps margin to the REC3 start-up (18 V max plus
the SS16 reverse-polarity drop) and to the 33 V PTC/TVS limit; a 24 V
supply or the MDT STC-1280.01 30 V output are both inside.

- `enclosure/cover_embossed.stl` (also `.step`): the cover with the legend
  recessed 0.6 mm into its faces, for single-colour printing.

## Hand-fitted parts (`<board>_hand_fit.csv`)

- Main J1: Phoenix 1574200 KNX pin strip. The red/black KNX plug goes in from
  the front into a cover pocket sized for the WAGO 243-211 (11.5 x 10.2 x 10.2 mm,
  measured, 0.3 mm clearance all round, a slot for the butterfly key on the
  right wall). It sits directly on the strip, where its sockets meet the pins;
  its wire entries face down, about 2.8 mm inside the open bottom of the
  pocket, and its top stays 1.3 mm behind the bottom shoulder face.
- Main U3: RECOM REC3-2415SRW/H2/A/CTRL (DIP-24, A pinning with pin 1 CTRL; clip unused pins 3 and 11 flush).
- Main C4: 470 uF 35 V, D10 x 16 (SamYoung KMG35V470M10*16 LO, LCSC C165500), **lying down
  on the back**: bend both leads 90 deg 3 mm from the body, insert from the
  back so the body axis is 7 mm below the board (2 mm air gap) and runs
  towards the KNX end, solder on the front, trim. It rests in two cradles in
  the base; the leads do not carry it. Minus stripe to pad 2 (round pad).
- UI U2: Seeed XIAO ESP32C6 **Pre-Soldered (SKU 102010636)**, detachable in
  two 1x7 8.5 mm female headers soldered to the back of the UI board (the bare
  113991254 ships without pin headers); module 11 mm above the board. Silkscreen marks
  USB, D0 and 5V. For USB flashing unsnap the UI board (it stays on its cable)
  or pull the XIAO out; with the board in the cover the protrusion wall
  blocks a straight USB-C plug.
- UI J2: Winstar **WEA012864DWPP3N00003** (WEA012864D-03, 0.96" 128x64
  SSD1306 I2C, white; `...DLPP...` yellow, `...DBPP...` sky blue), pin order
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
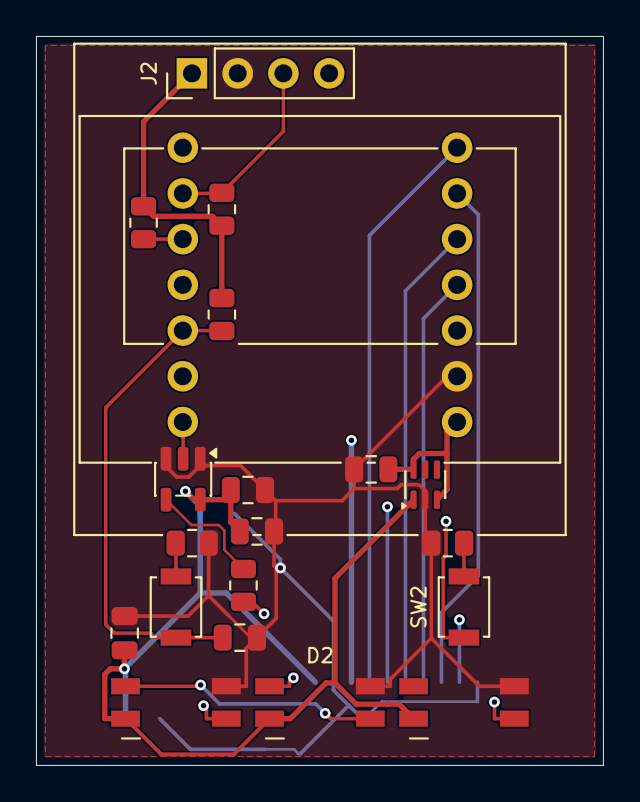
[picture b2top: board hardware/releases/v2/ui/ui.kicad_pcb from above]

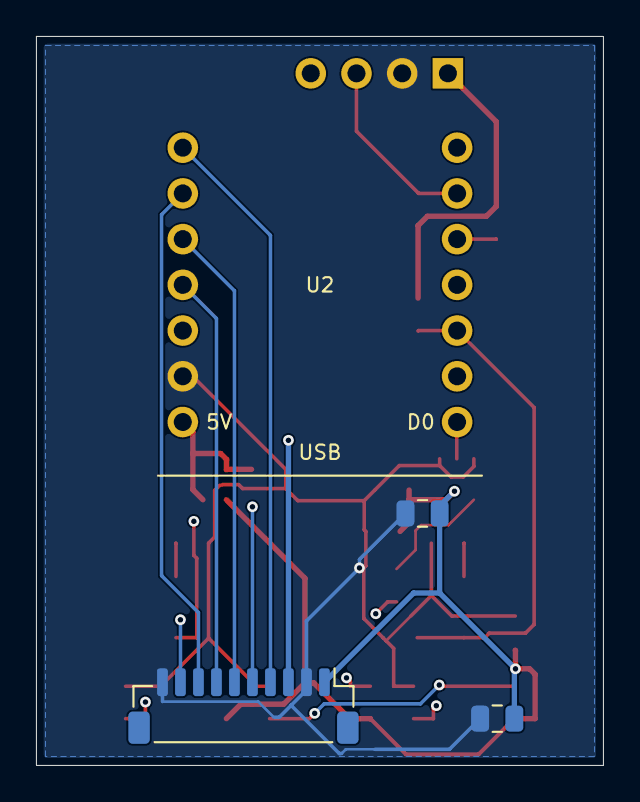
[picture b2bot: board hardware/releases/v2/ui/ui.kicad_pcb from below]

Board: 4 copper layers, 31.5 x 40.5 mm, 23 parts (4 on the bottom side), 20 nets.

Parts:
C1: 10u 25V; C_0805_2012Metric
C2, C4, C5, C6, C7: 100n 50V; C_0805_2012Metric
C3: 1u 50V; C_0805_2012Metric
D1: RGB STATUS; LED_WS2812B-MINI-V3J_3.5x3.5mm
D2: RGB KNX; LED_WS2812B-MINI-V3J_3.5x3.5mm
D3: RGB DALI; LED_WS2812B-MINI-V3J_3.5x3.5mm
J1: Controller cable; JST_SH_BM10B-SRSS-TB_1x10-1MP_P1.00mm_Vertical
J2: OLED; PinHeader_1x04_P2.54mm_Vertical
R1, R2: 4k7; R_0805_2012Metric
R3, R4: 10k; R_0805_2012Metric
R5: 20k; R_0805_2012Metric
R6: 330R; R_0805_2012Metric
SW1: SCROLL; SW_SPST_B3U-1000P
SW2: RESET; SW_SPST_B3U-1000P
U1: LM66100; SOT-363_SC-70-6
U2: XIAO ESP32C6; XIAO_ESP32C6_Header
U3: 74AHCT1G125; SOT-23-5

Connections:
+3V3: J1.3, J2.1, R1.1, R2.1, R3.1, U2.12
+5V: C3.1, C4.1, C5.1, C6.1, C7.1, D1.1, D2.1, D3.1, J1.1, U1.1, U3.5
+5V_XIAO: C1.1, U1.3, U1.6, U2.14
BTN_LADDER: C2.1, R3.2, SW1.1, SW2.1, U2.3
DALI_RX: J1.8, U2.9
DALI_SUPPLY_OFF: J1.9, U2.2
DALI_TX: J1.7, U2.11
GND: C1.2, C2.2, C3.2, C4.2, C5.2, C6.2, C7.2, D1.3, D2.3, D3.3, J1.2, J1.10, J2.2, R4.2, R5.2, U1.2, U2.13, U3.1, U3.3
I2C_SCL: J2.3, R2.2, U2.6
I2C_SDA: J2.4, R1.2, U2.5
KNX_RXD: J1.5, U2.7
KNX_TXD: J1.4, U2.8
LED_CHAIN1: D1.2, D2.4
LED_CHAIN2: D2.2, D3.4
LED_DATA: U2.1, U3.2
unnamed: R4.1, SW1.2
unnamed: R5.1, SW2.2
unnamed: R6.1, U3.4
unnamed: D1.4, R6.2
NCN_SAVEB: J1.6, U2.10

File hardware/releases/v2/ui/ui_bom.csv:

Designator,Quantity,Value,Footprint,Manufacturer Part Number,LCSC Part #,Mount,Fitted by
"C2,C4,C5,C6,C7",5,100n 50V,C_0805_2012Metric,CC0805KRX7R9BB104,C49678,SMD,assembler
"R3,R4",2,10k,R_0805_2012Metric,0805W8F1002T5E,C17414,SMD,assembler
C1,1,10u 25V,C_0805_2012Metric,CL21A106KAYNNNE,C15850,SMD,assembler
C3,1,1u 50V,C_0805_2012Metric,CL21B105KBFNNNE,C28323,SMD,assembler
R5,1,20k,R_0805_2012Metric,0805W8F2002T5E,C4328,SMD,assembler
R6,1,330R,R_0805_2012Metric,0805W8F3300T5E,C17630,SMD,assembler
"R1,R2",2,4k7,R_0805_2012Metric,0805W8F4701T5E,C17673,SMD,assembler
U3,1,74AHCT1G125,SOT-23-5,SN74AHCT1G125DBVR,C7484,SMD,assembler
J1,1,Controller cable,JST_SH_BM10B-SRSS-TB_1x10-1MP_P1.00mm_Vertical,BM10B-SRSS-TB(LF)(SN),C160396,SMD,assembler
U1,1,LM66100,SOT-363_SC-70-6,LM66100DCKR,C2869734,SMD,assembler
SW2,1,RESET,SW_SPST_B3U-1000P,B3U-1000P,C231329,SMD,assembler
D3,1,RGB DALI,LED_WS2812B-MINI-V3J_3.5x3.5mm,WS2812B-MINI-V3J,C22371519,SMD,assembler
D2,1,RGB KNX,LED_WS2812B-MINI-V3J_3.5x3.5mm,WS2812B-MINI-V3J,C22371519,SMD,assembler
D1,1,RGB STATUS,LED_WS2812B-MINI-V3J_3.5x3.5mm,WS2812B-MINI-V3J,C22371519,SMD,assembler
SW1,1,SCROLL,SW_SPST_B3U-1000P,B3U-1000P,C231329,SMD,assembler
J2,1,OLED,PinHeader_1x04_P2.54mm_Vertical,WEA012864DWPP3N00003,,THT,hand-fit (not assembled)
U2,1,XIAO ESP32C6,XIAO_ESP32C6_Header,102010636,,THT,hand-fit (not assembled)

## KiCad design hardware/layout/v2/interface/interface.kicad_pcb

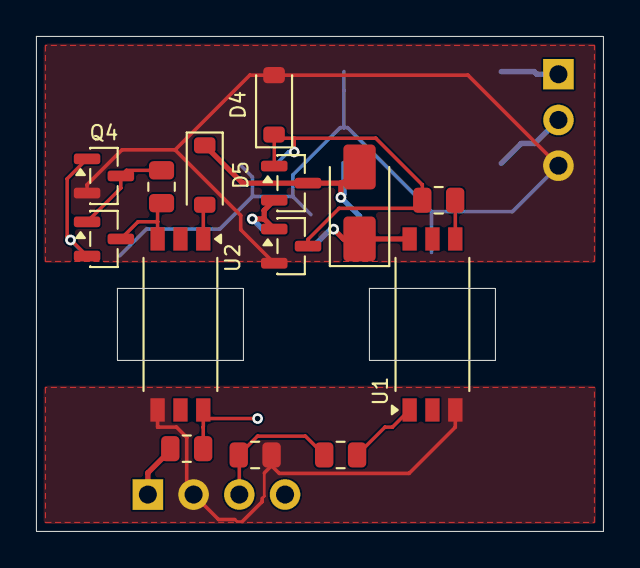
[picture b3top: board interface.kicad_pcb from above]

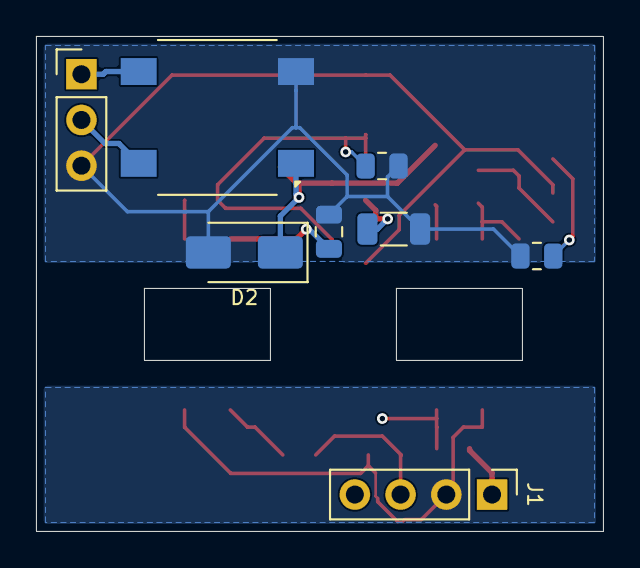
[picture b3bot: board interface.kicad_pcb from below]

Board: 4 copper layers, 31.5 x 27.5 mm, 22 parts (8 on the bottom side), 17 nets.

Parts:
C1: 1u 50V; C_0805_2012Metric
D1: DF06S; Diode_Bridge_Vishay_DFS
D2: SMAJ24A; D_SMA
D3: SS16; D_SMA
D4: 12V; D_SOD-123
D5: 5V6; D_SOD-123
J1: Main logic; PinHeader_1x04_P2.54mm_Vertical
J2: Main DALI; PinHeader_1x03_P2.54mm_Vertical
Q1: IRLML0060; SOT-23
Q2, Q3, Q4: BC847; SOT-23
R1: 330R; R_0805_2012Metric
R2, R4: 10k; R_0805_2012Metric
R3, R8: 4k7; R_0805_2012Metric
R5: 2R; R_1206_3216Metric
R6: 100k; R_0805_2012Metric
R7: 680R; R_0805_2012Metric
U1, U2: TLP383(D4BLLTL,E; SO-6L_10x3.84mm_P1.27mm

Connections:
+3V3: J1.1, R8.1
DA1: D1.3, J2.1
DA2: D1.4, J2.2
DALI_BOOT: C1.1, D3.1, U1.6
DALI_GATE: D4.1, Q1.1, Q2.3, R3.2, R4.1
DALI_GATE_SW: R3.1, U1.4
DALI_RX: J1.4, R8.2, U2.6
DALI_SENSE: Q1.2, Q2.1, R5.1
DALI_TX: J1.3, R1.1, R2.1
DA_P: D1.1, D2.1, D3.2, D5.1, Q1.3
GND: J1.2, R2.2, U1.3, U2.4
GNDD: C1.2, D1.2, D2.2, D4.2, J2.3, Q2.2, Q4.2, R4.2, R5.2, R7.2
unnamed: R1.2, U1.1
unnamed: D5.2, U2.1
unnamed: Q3.2, Q4.1, R7.1
unnamed: Q3.1, Q4.3, R6.2
RX_LIM_IN: Q3.3, R6.1, U2.3

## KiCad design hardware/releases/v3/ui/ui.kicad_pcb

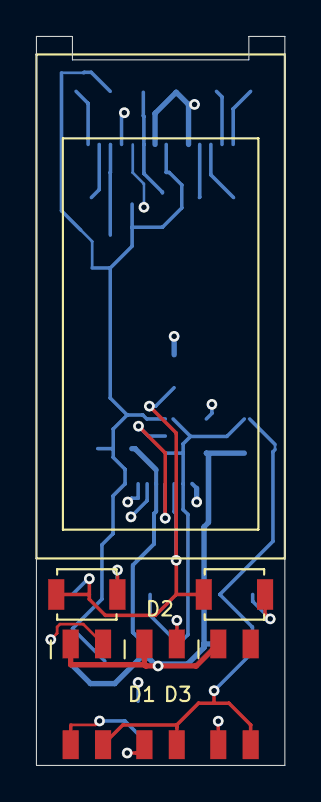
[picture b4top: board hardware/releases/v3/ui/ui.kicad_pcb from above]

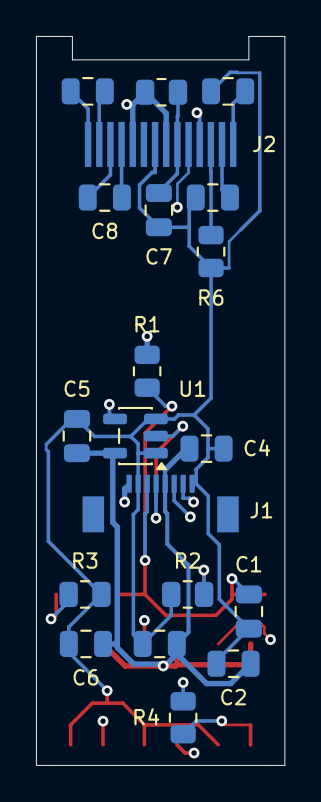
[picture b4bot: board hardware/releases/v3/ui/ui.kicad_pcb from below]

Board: 4 copper layers, 13.8 x 40.5 mm, 25 parts (20 on the bottom side), 21 nets.

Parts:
C1, C3, C4, C5, C6, C7: 100n 50V; C_0805_2012Metric
C2, C8, C9, C10, C11: 1u 50V; C_0805_2012Metric
D1: RGB STATUS; LED_WS2812B-MINI-V3J_3.5x3.5mm
D2: RGB KNX; LED_WS2812B-MINI-V3J_3.5x3.5mm
D3: RGB DALI; LED_WS2812B-MINI-V3J_3.5x3.5mm
J1: Carrier; FPC_Kinghelm_KH-FPC0.5-H1.2SMT-8P
J2: OLED; OLED_FPC_14P_P0.62mm_Hotbar
R1, R2, R5: 10k; R_0805_2012Metric
R3: 20k; R_0805_2012Metric
R4: 330R; R_0805_2012Metric
R6: 390k; R_0805_2012Metric
SW1: SCROLL; SW_SPST_B3U-1000P
SW2: RESET; SW_SPST_B3U-1000P
U1: 74AHCT1G125; SOT-23-5

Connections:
+3V3: J1.1, J2.5, J2.8, R1.1, R5.1
+5V: C2.1, C3.1, C4.1, C5.1, C6.1, D1.1, D2.1, D3.1, J1.5, U1.5
BTN_LADDER: C1.1, J1.3, R1.2, SW1.1, SW2.1
GND: C1.2, C2.2, C3.2, C4.2, C5.2, C6.2, C7.2, C10.2, C11.2, D1.3, D2.3, D3.3, J1.2, J1.8, J2.7, R2.2, R3.2, R6.2, U1.1, U1.3
I2C_SCL: J1.7, J2.10
I2C_SDA: J1.6, J2.11
LED_CHAIN1: D1.2, D2.4
LED_CHAIN2: D2.2, D3.4
LED_DATA: J1.4, U1.2
unnamed: R2.1, SW1.2
unnamed: R3.1, SW2.2
unnamed: R4.1, U1.4
unnamed: D1.4, R4.2
OLED_C1N: C8.2, J2.4
OLED_C1P: C8.1, J2.3
OLED_C2N: C9.2, J2.2
OLED_C2P: C9.1, J2.1
OLED_IREF: J2.12, R6.1
OLED_RES: C7.1, J2.9, R5.2
OLED_VCOMH: C10.1, J2.13
OLED_VOUT: C11.1, J2.14
